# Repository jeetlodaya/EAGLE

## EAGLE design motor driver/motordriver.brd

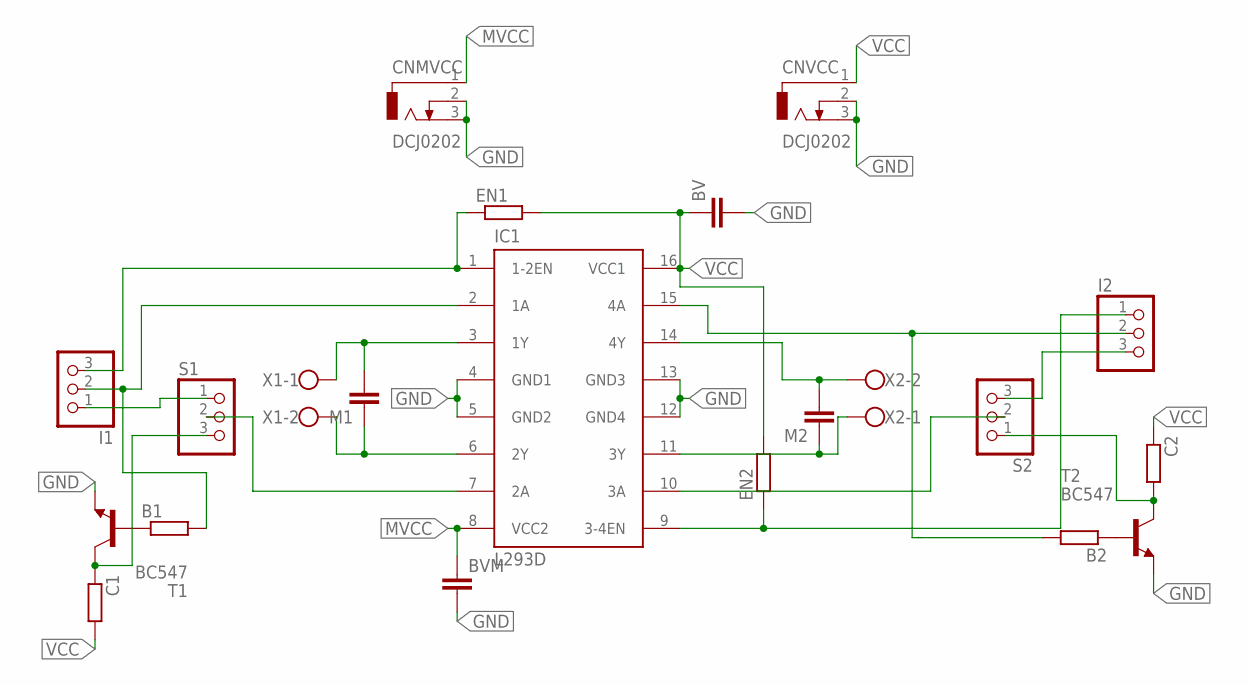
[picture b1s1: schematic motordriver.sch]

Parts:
B1, B2: R-EU_0204/7; 0204/7
BV: C2.5/2; C2.5-2
BVM: C-EU050-025X075; C050-025X075
C1, C2: R-EU_0204/7; 0204/7
CNMVCC: DCJ0202
CNVCC: DCJ0202
EN1, EN2: R-EU_0204/7; 0204/7
I1, I2: PINHD-1X3; 1X03
IC1: L293D; DIL16
M1, M2: C2.5/2; C2.5-2
S1, S2: PINHD-1X3; 1X03
T1, T2: BC547; TO92
X1, X2: W237-102

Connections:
GND: BV.2, BVM.2, CNMVCC.2, CNMVCC.3, CNVCC.2, CNVCC.3, IC1.4 (GND1), IC1.5 (GND2), IC1.12 (GND4), IC1.13 (GND3), T1.1 (E), T2.1 (E)
MVCC: BVM.1, CNMVCC.1, IC1.8 (VCC2)
unnamed: EN2.1, I2.1, IC1.9 (3-4EN)
unnamed: IC1.3 (1Y), M1.2, X1.1
unnamed: IC1.6 (2Y), M1.1, X1.2
unnamed: EN1.1, I1.3, IC1.1 (1-2EN)
unnamed: IC1.14 (4Y), M2.2, X2.2
unnamed: IC1.11 (3Y), M2.1, X2.1
unnamed: C1.1, S1.3, T1.3 (C)
unnamed: I2.3, S2.3
unnamed: B1.1, T1.2 (B)
unnamed: B2.1, T2.2 (B)
unnamed: I1.1, S1.1
unnamed: B1.2, I1.2, IC1.2 (1A)
unnamed: IC1.7 (2A), S1.2
unnamed: C2.2, S2.1, T2.3 (C)
unnamed: IC1.10 (3A), S2.2
unnamed: B2.2, I2.2, IC1.15 (4A)
VCC: BV.1, C1.2, C2.1, CNVCC.1, EN1.2, EN2.2, IC1.16 (VCC1)

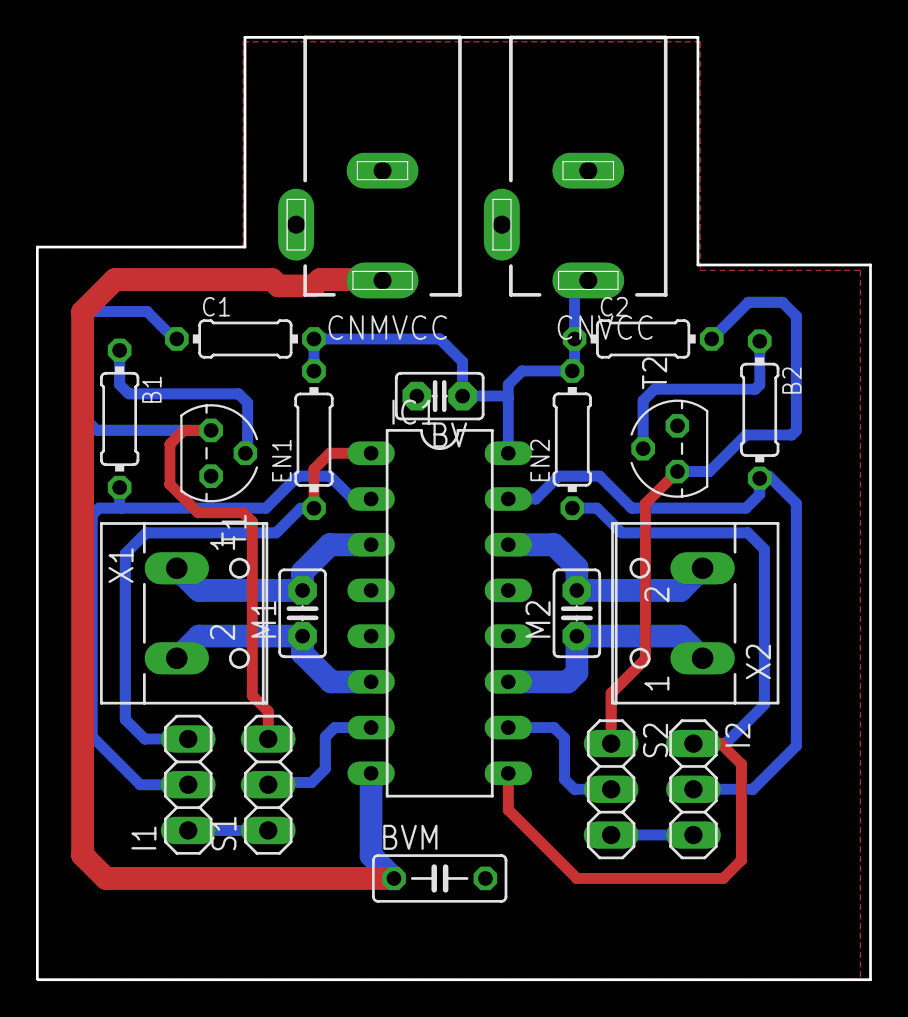
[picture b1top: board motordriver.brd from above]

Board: 2 copper layers, 46.3 x 52.4 mm, 21 parts (0 on the bottom side), 19 nets.

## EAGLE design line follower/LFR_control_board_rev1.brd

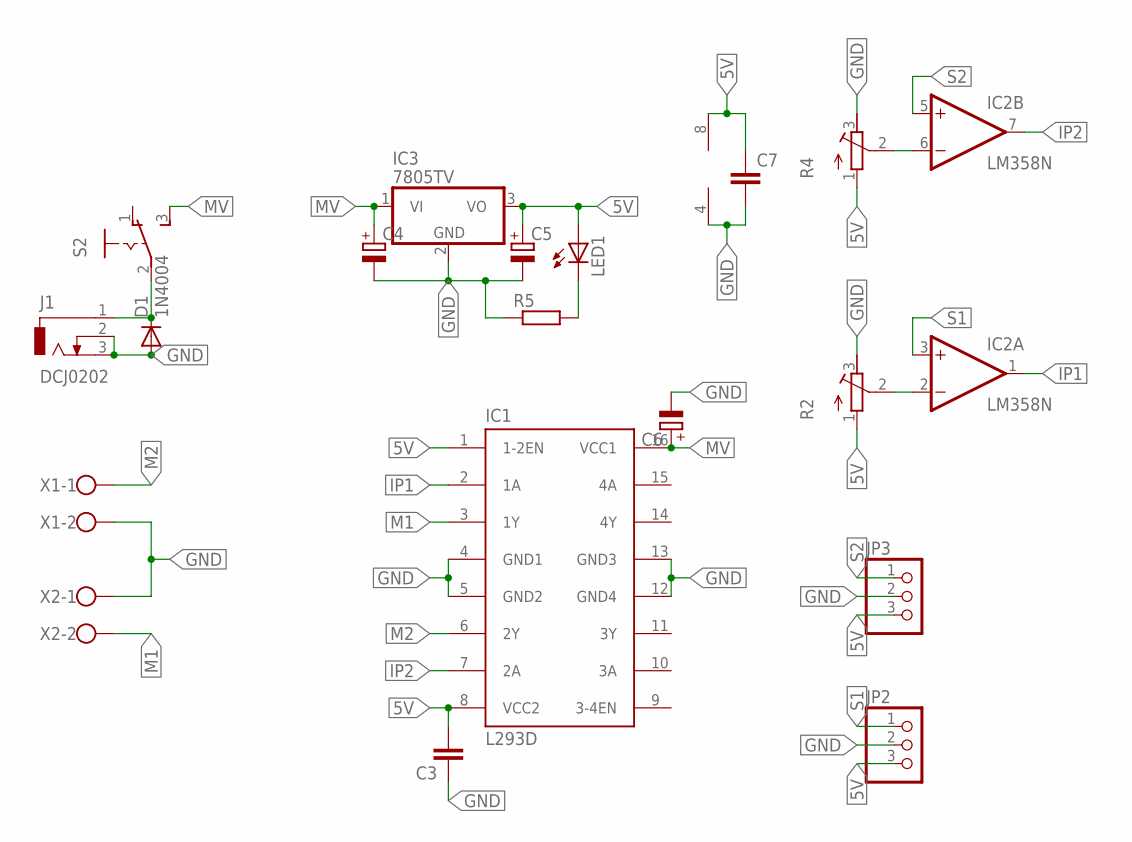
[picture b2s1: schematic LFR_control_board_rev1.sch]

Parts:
C3, C7: C-EU025-025X050; C025-025X050
C4, C5: CPOL-EUE2,5-6E; E2,5-6E
C6: CPOL-EUE5-10.5; E5-10,5
D1: 1N4004; DO41-10
IC1: L293D; DIL16
IC2: LM358N; DIL08
IC3: 7805TV; TO220V
J1: DCJ0202
JP2, JP3: PINHD-1X3; 1X03
LED1: LED5MM
R2, R4: R-TRIMM3296W; RTRIM3296W
R5: R-EU_0207/10; 0207/10
S2: 255SB
X1, X2: W237-102

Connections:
5V: C3.2, C5.+, C7.1, IC1.1 (1-2EN), IC1.8 (VCC2), IC2.8 (V+), IC3.3 (VO), JP2.3, JP3.3, LED1.A, R2.1 (A), R4.1 (A)
GND: C3.1, C4.-, C5.-, C6.-, C7.2, D1.A, IC1.4 (GND1), IC1.5 (GND2), IC1.12 (GND4), IC1.13 (GND3), IC2.4 (V-), IC3.2 (GND), J1.2, J1.3, JP2.2, JP3.2, R2.3 (E), R4.3 (E), R5.1, X1.2, X2.1
IP1: IC1.2 (1A), IC2.1 (OUT)
IP2: IC1.7 (2A), IC2.7 (OUT)
M1: IC1.3 (1Y), X2.2
M2: IC1.6 (2Y), X1.1
MV: C4.+, C6.+, IC1.16 (VCC1), IC3.1 (VI), S2.3 (S)
unnamed: IC2.2 (-IN), R2.2 (S)
unnamed: D1.C, J1.1, S2.2
unnamed: LED1.K (C), R5.2
unnamed: IC2.6 (-IN), R4.2 (S)
S1: IC2.3 (+IN), JP2.1
S2: IC2.5 (+IN), JP3.1

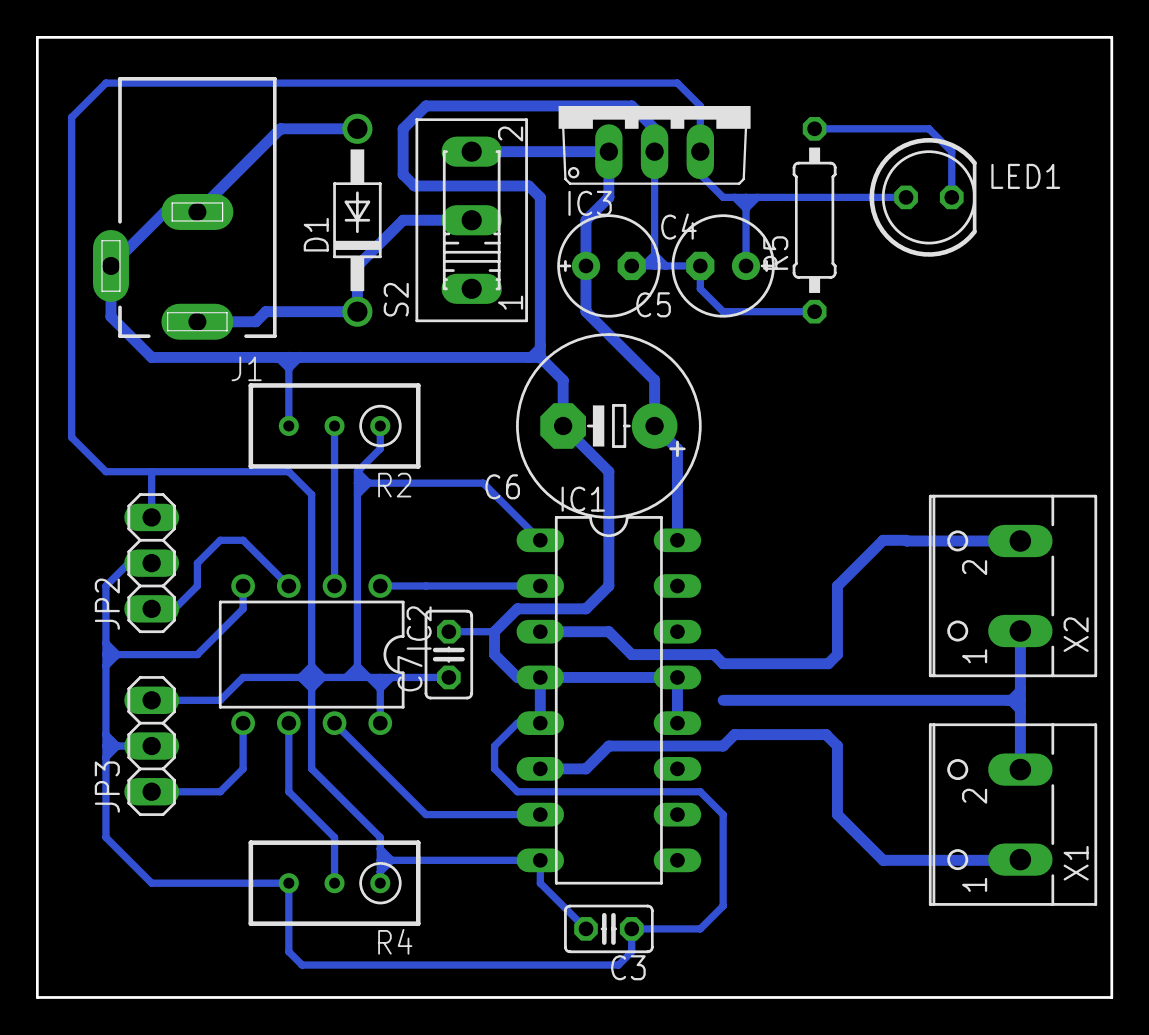
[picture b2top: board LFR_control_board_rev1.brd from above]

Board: 2 copper layers, 59.7 x 53.3 mm, 19 parts (0 on the bottom side), 13 nets.

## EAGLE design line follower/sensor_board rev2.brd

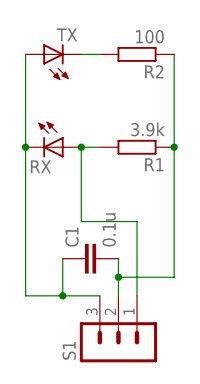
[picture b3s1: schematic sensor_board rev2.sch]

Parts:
C1: 0.1u; C025-025X050
R1: 3.9k; 0207/10
R2: 100; 0207/10
RX: LED5MM
S1: MA03-1
TX: LED5MM

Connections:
unnamed: C1.1, RX.K (C), S1.3, TX.A
unnamed: R2.2, TX.K (C)
unnamed: C1.2, R1.1, R2.1, S1.2
unnamed: R1.2, RX.A, S1.1

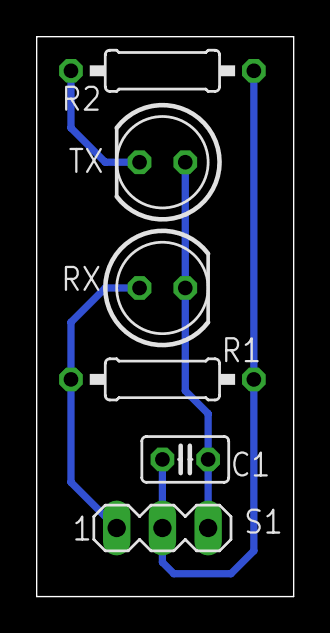
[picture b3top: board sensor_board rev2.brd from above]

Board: 2 copper layers, 14.3 x 31.1 mm, 6 parts (0 on the bottom side), 4 nets.

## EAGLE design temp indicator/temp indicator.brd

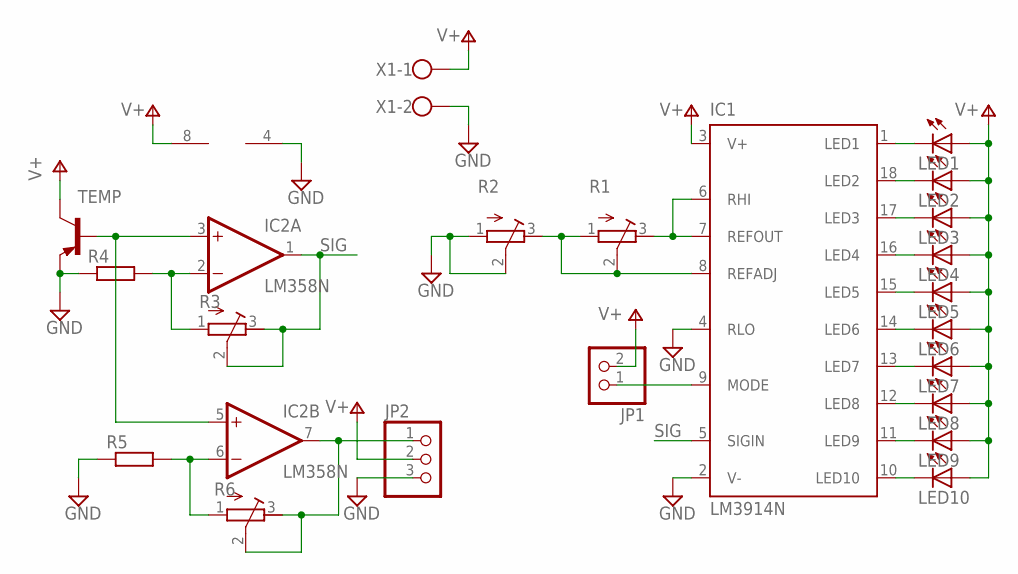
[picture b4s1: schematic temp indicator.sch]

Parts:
IC1: LM3914N; DIL18
IC2: LM358N; DIL08
JP1: PINHD-1X2; 1X02
JP2: PINHD-1X3; 1X03
LED1, LED2, LED3, LED4, LED5, LED6, LED7, LED8, LED9, LED10: LED5MM
R1, R2, R3, R6: R-TRIMM64W; RTRIM64W
R4, R5: R-EU_0207/10; 0207/10
TEMP: BC557; TO92-EBC
X1: W237-102

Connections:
GND: IC1.2 (V-), IC1.4 (RLO), IC2.4 (V-), JP2.3, R2.1 (A), R2.2 (S), R4.1, R5.1, TEMP.E, X1.2
unnamed: IC1.1 (LED1), LED1.K (C)
unnamed: IC1.18 (LED2), LED2.K (C)
unnamed: IC1.17 (LED3), LED3.K (C)
unnamed: IC1.16 (LED4), LED4.K (C)
unnamed: IC1.15 (LED5), LED5.K (C)
unnamed: IC1.14 (LED6), LED6.K (C)
unnamed: IC1.13 (LED7), LED7.K (C)
unnamed: IC1.12 (LED8), LED8.K (C)
unnamed: IC1.11 (LED9), LED9.K (C)
unnamed: IC1.10 (LED10), LED10.K (C)
unnamed: IC1.6 (RHI), IC1.7 (REFOUT), R1.3 (E)
unnamed: IC1.9 (MODE), JP1.1
unnamed: IC1.8 (REFADJ), R1.1 (A), R1.2 (S), R2.3 (E)
unnamed: IC2.7 (OUT), JP2.1, R6.2 (S), R6.3 (E)
unnamed: IC2.3 (+IN), IC2.5 (+IN), TEMP.B
unnamed: IC2.2 (-IN), R3.1 (A), R4.2
unnamed: IC2.6 (-IN), R5.2, R6.1 (A)
SIG: IC1.5 (SIGIN), IC2.1 (OUT), R3.2 (S), R3.3 (E)
V+: IC1.3 (V+), IC2.8 (V+), JP1.2, JP2.2, LED1.A, LED2.A, LED3.A, LED4.A, LED5.A, LED6.A, LED7.A, LED8.A, LED9.A, LED10.A, TEMP.C, X1.1

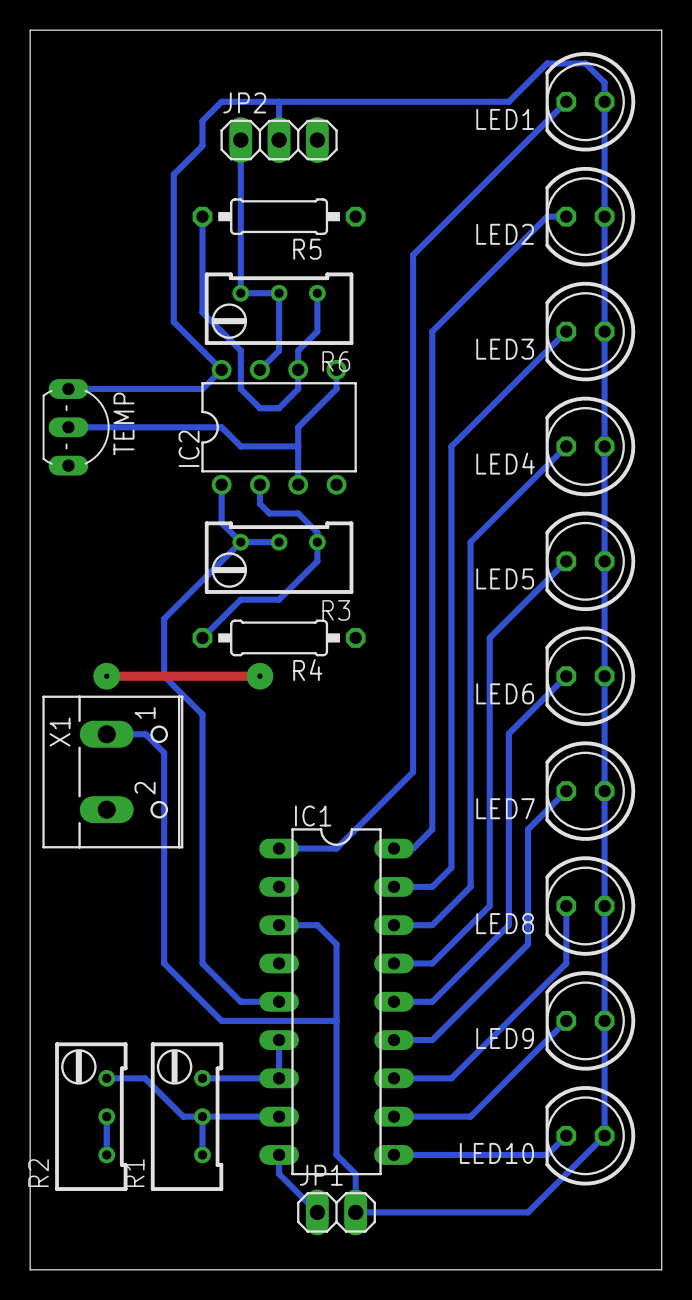
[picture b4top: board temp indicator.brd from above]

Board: 2 copper layers, 41.9 x 82.2 mm, 22 parts (0 on the bottom side), 20 nets.

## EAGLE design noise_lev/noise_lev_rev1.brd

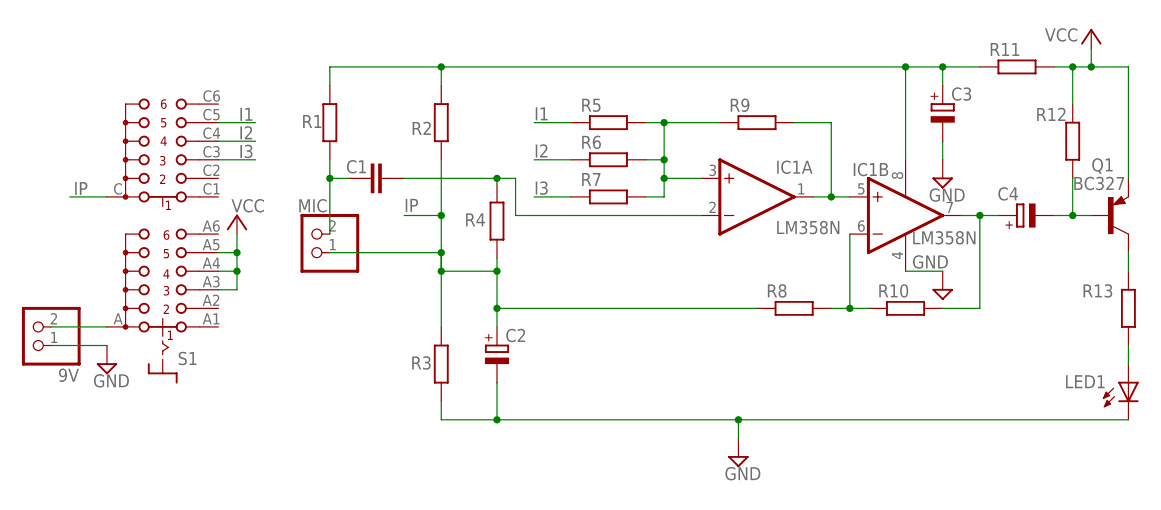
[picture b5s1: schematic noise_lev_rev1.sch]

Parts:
9V: PINHD-1X2; 1X02
C1: C-EU025-025X050; C025-025X050
C2, C4: CPOL-EUE2.5-5; E2,5-5
C3: CPOL-EUE5-10.5; E5-10,5
IC1: LM358N; DIL08
LED1: LED5MM
MIC: PINHD-1X2; 1X02
Q1: BC327; TO92-EBC
R1, R2, R3, R4, R5, R6, R7, R8, R9, R10, R11, R12, R13: R-EU_0207/10; 0207/10
S1: CK102X06

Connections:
GND: 9V.1, C2.-, C3.-, IC1.4 (V-), LED1.K (C), R3.1
I1: R5.1, S1.C5
I2: R6.1, S1.C4
I3: R7.1, S1.C3
IP: C2.+, MIC.1, R2.1, R3.2, R4.2, R8.1, S1.C
unnamed: IC1.3 (+IN), R5.2, R6.2, R7.2, R9.1
unnamed: Q1.C, R13.2
unnamed: LED1.A, R13.1
unnamed: IC1.1 (OUT), IC1.5 (+IN), R9.2
unnamed: C4.-, Q1.B, R12.1
unnamed: 9V.2, S1.A
unnamed: IC1.6 (-IN), R8.2, R10.1
unnamed: C1.2, IC1.2 (-IN), R4.1
unnamed: C1.1, MIC.2, R1.1
unnamed: C4.+, IC1.7 (OUT), R10.2
unnamed: C3.+, IC1.8 (V+), R1.2, R2.2, R11.1
VCC: Q1.E, R11.2, R12.2, S1.A3, S1.A4, S1.A5

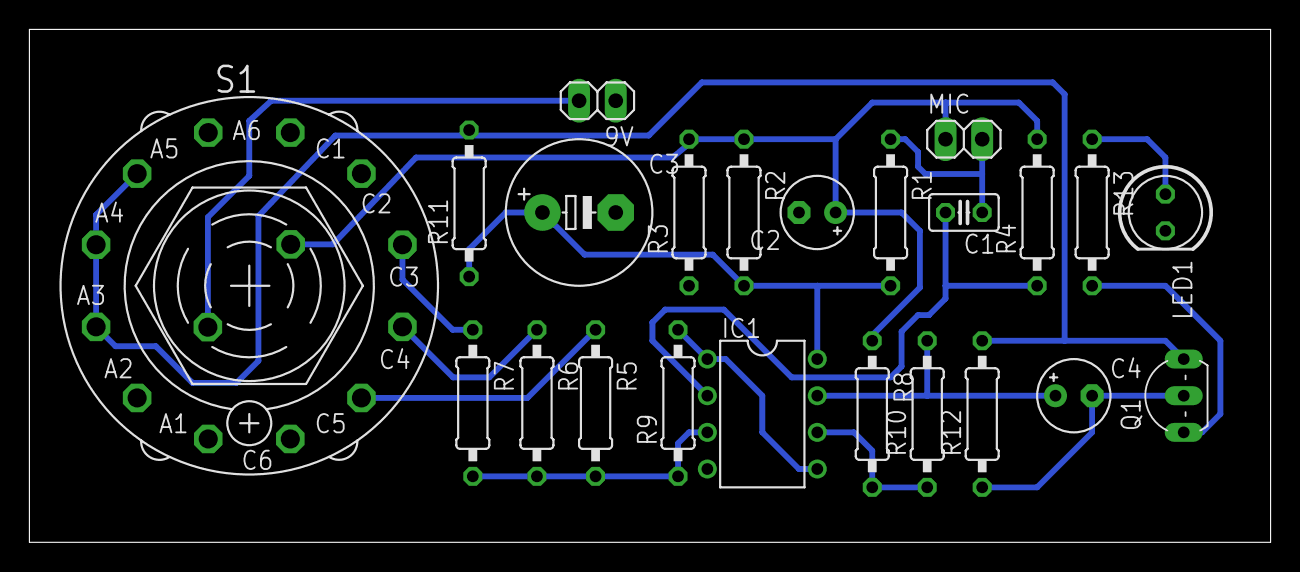
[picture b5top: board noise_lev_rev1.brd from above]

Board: 2 copper layers, 86.0 x 35.6 mm, 23 parts (0 on the bottom side), 17 nets.

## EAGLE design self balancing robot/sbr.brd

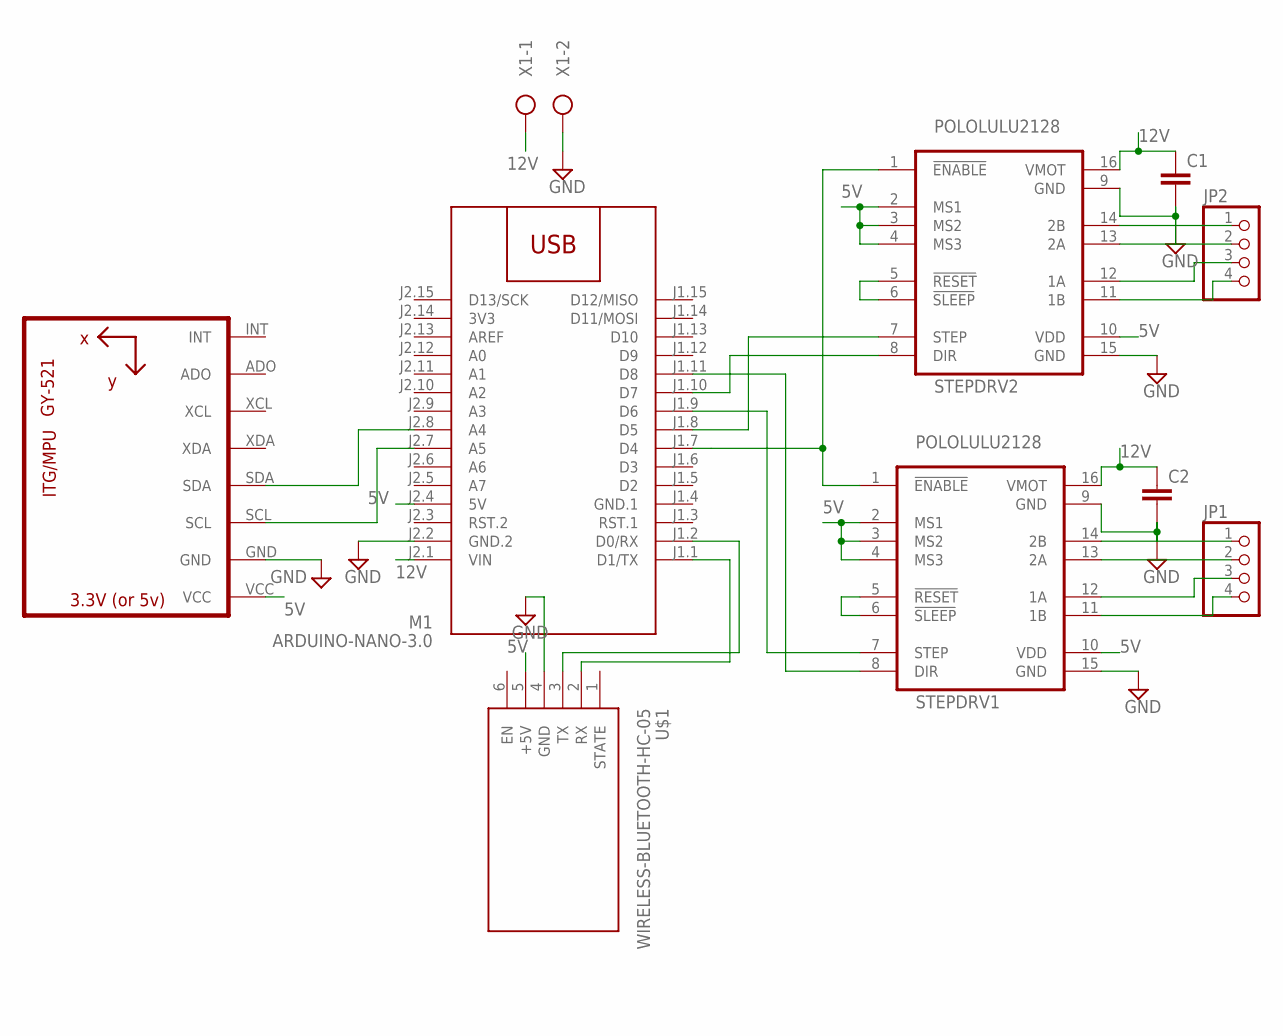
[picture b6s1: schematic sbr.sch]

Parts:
C1, C2: C-EU025-024X044; C025-024X044
JP1, JP2: PINHD-1X4; 1X04
M1: ARDUINO-NANO-3.0
STEPDRV1, STEPDRV2: POLOLULU2128
U1: GY-521MPU6050; GY-521
U$1: WIRELESS-BLUETOOTH-HC-05
X1: W237-102

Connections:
3V3: M1.J2.14 (3V3)
5V: M1.J2.4 (5V), STEPDRV1.2 (MS1), STEPDRV1.3 (MS2), STEPDRV1.4 (MS3), STEPDRV1.10 (VDD), STEPDRV2.2 (MS1), STEPDRV2.3 (MS2), STEPDRV2.4 (MS3), STEPDRV2.10 (VDD), U1.VCC, U$1.5 (+5V)
12V: C1.1, C2.1, M1.J2.1 (VIN), STEPDRV1.16 (VMOT), STEPDRV2.16 (VMOT), X1.1
GND: C1.2, C2.2, M1.J2.2 (GND.2), STEPDRV1.9 (GND), STEPDRV1.15 (GND), STEPDRV2.9 (GND), STEPDRV2.15 (GND), U1.GND, U$1.4 (GND), X1.2
GND.1: M1.J1.4 (GND.1)
unnamed: JP2.1, STEPDRV2.14 (2B)
unnamed: M1.J1.8 (D5), STEPDRV2.7 (STEP)
unnamed: M1.J1.9 (D6), STEPDRV1.7 (STEP)
unnamed: JP1.1, STEPDRV1.14 (2B)
unnamed: JP1.2, STEPDRV1.13 (2A)
unnamed: JP1.3, STEPDRV1.12 (1A)
unnamed: JP1.4, STEPDRV1.11 (1B)
unnamed: JP2.2, STEPDRV2.13 (2A)
unnamed: JP2.3, STEPDRV2.12 (1A)
unnamed: JP2.4, STEPDRV2.11 (1B)
unnamed: STEPDRV2.5 (!RESET), STEPDRV2.6 (!SLEEP)
unnamed: STEPDRV1.5 (!RESET), STEPDRV1.6 (!SLEEP)
unnamed: M1.J1.7 (D4), STEPDRV1.1 (!ENABLE), STEPDRV2.1 (!ENABLE)
unnamed: M1.J1.1 (D1/TX), U$1.2 (RX)
unnamed: M1.J1.2 (D0/RX), U$1.3 (TX)
unnamed: M1.J2.8 (A4), U1.SDA
unnamed: M1.J2.7 (A5), U1.SCL
unnamed: M1.J1.10 (D7), STEPDRV2.8 (DIR)
unnamed: M1.J1.11 (D8), STEPDRV1.8 (DIR)

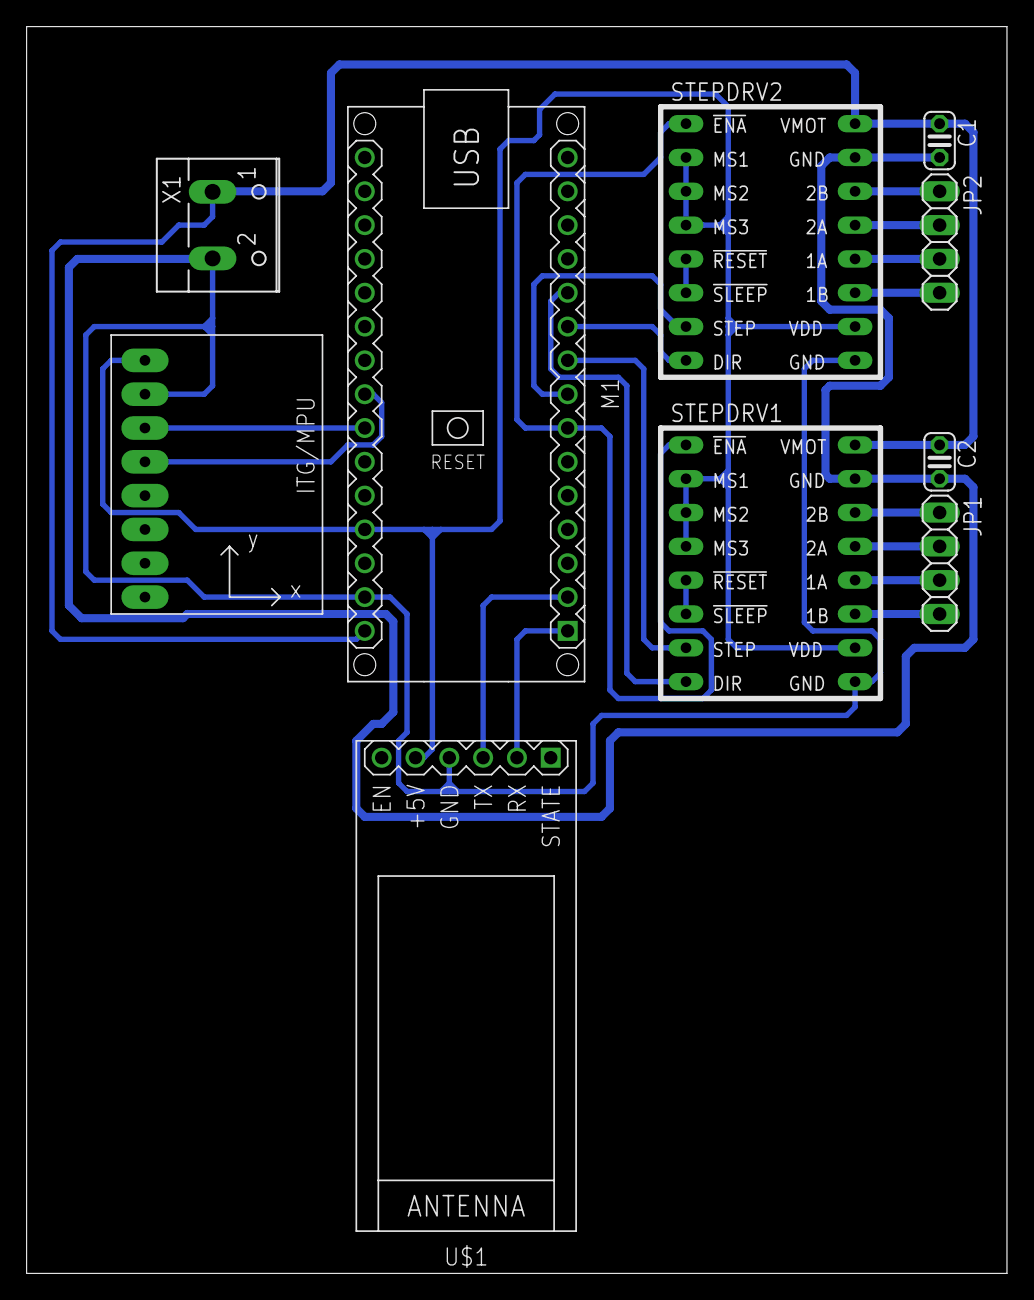
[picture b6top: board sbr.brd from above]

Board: 2 copper layers, 73.6 x 93.6 mm, 10 parts (0 on the bottom side), 22 nets.

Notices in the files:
parts and their libraries:
diy-modules: Released under the Creative Commons Attribution 4.0 International License: http://creativecommons.org/licenses/by/4.0
